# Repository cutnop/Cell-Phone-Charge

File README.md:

# Cell-Phone-Charger

1) Install eagle
2) Download the Sparkfun and Adafruit lbr. from the websites and save in the eagle lbr folder
3) Download the extra Eagle lbr's from this github and also save in the lbr folder

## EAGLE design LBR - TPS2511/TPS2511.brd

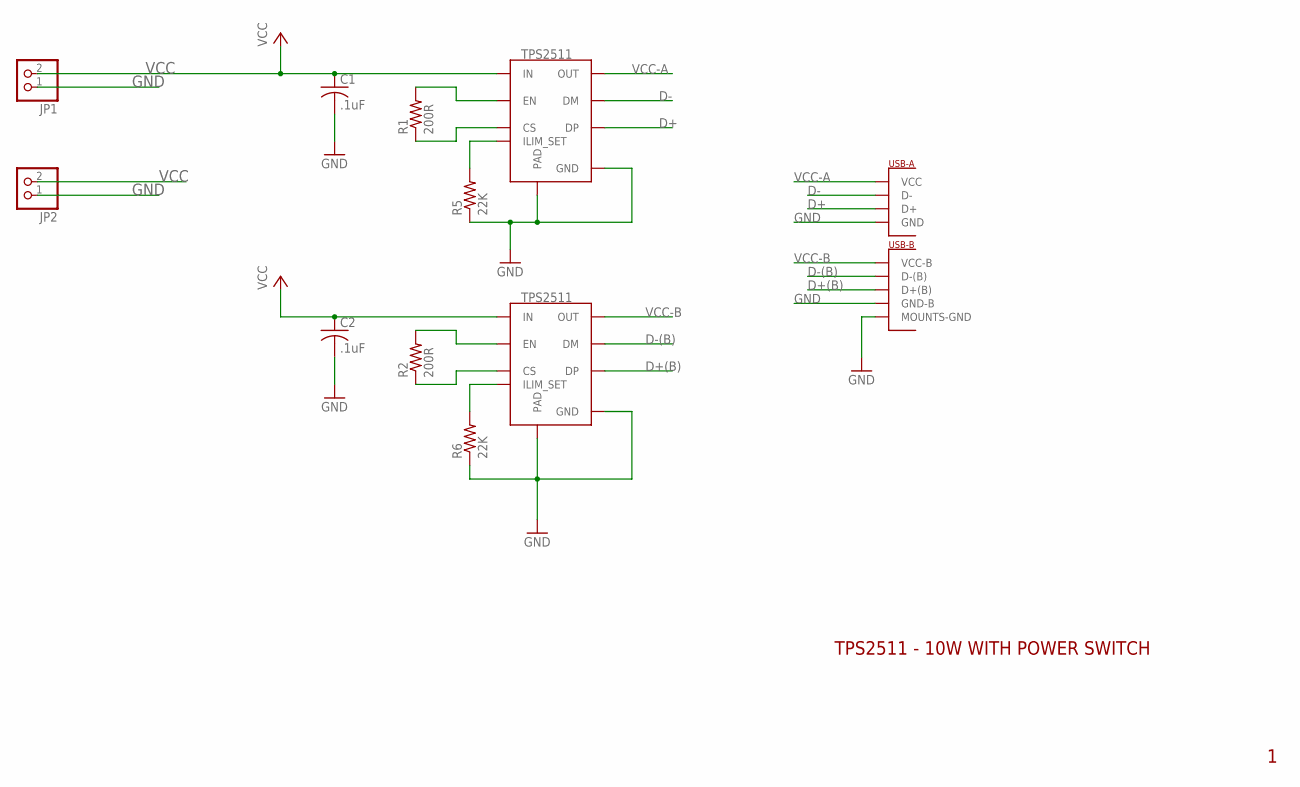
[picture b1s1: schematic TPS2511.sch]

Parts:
C1, C2: .1uF; C050-024X044
JP1, JP2: PINHD-1X2/90; 1X02/90
R1, R2: 200R; 0204/7
R5, R6: 22K; 0204/7
U$1, U$3: TPS2511-MSOP8; MSOP-8
U$2: DUAL-PORT-USB-REC; DUAL-PORT-USB

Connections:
D+: U$1.P$6 (DP), U$2.P$8 (D+)
D+(B): U$2.P$6 (D+(B)), U$3.P$6 (DP)
D-: U$1.P$7 (DM), U$2.P$7 (D-)
D-(B): U$2.P$5 (D-(B)), U$3.P$7 (DM)
GND: C1.2, C2.2, JP1.1, JP2.1, R5.1, R6.1, U$1.P$1 (GND), U$1.P$9 (PAD), U$2.GND (MOUNTS-GND), U$2.P$2 (MOUNTS-GND), U$2.P$3 (MOUNTS-GND), U$2.P$4 (MOUNTS-GND), U$2.P$9 (GND-B), U$2.P$11 (GND), U$3.P$1 (GND), U$3.P$9 (PAD)
unnamed: R5.2, U$1.P$2 (ILIM_SET)
unnamed: R6.2, U$3.P$2 (ILIM_SET)
unnamed: R1.2, U$1.P$5 (EN)
unnamed: R1.1, U$1.P$4 (CS)
unnamed: R2.2, U$3.P$5 (EN)
unnamed: R2.1, U$3.P$4 (CS)
VCC: C1.1, C2.1, JP1.2, JP2.2, U$1.P$3 (IN), U$3.P$3 (IN)
VCC-A: U$1.P$8 (OUT), U$2.P$12 (VCC)
VCC-B: U$2.P$10 (VCC-B), U$3.P$8 (OUT)

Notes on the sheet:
TPS2511 - 10W WITH POWER SWITCH

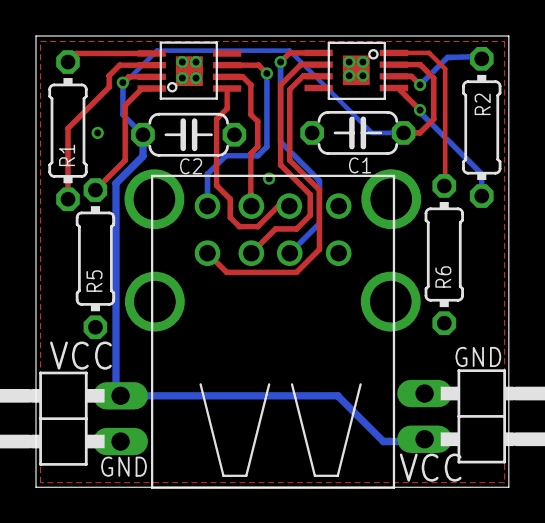
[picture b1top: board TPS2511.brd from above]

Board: 2 copper layers, 26.3 x 25.1 mm, 11 parts (0 on the bottom side), 14 nets.

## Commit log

2015-03-10 Added sch and extra lbr files
2015-03-31 Added more parts
2015-03-31 Create gh-pages branch via GitHub
